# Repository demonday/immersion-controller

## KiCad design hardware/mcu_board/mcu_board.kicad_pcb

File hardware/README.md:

"Smart" Immersion Controller

See https://www.notion.so/niallgormley/Smart-Domestic-Immersion-Heater-Controller-AquaHeatIQ-cdcf95fe5f9b4179aaec39e1e94fd0bb

# Notes

## 11/11/2023 - Initial Prototype Iteration

### Results from assembly and first tests.

- Incorrect Footprint for choke (L2)
- 3.3v Power has some high freq (~20kHz) noise, and some voltage drop when relays activated.
- Relay configuration. Insufficient capacity (10A, needs ~13A) on relay NC config that I used to ensure only one relay activates at any one time.
- I wired all the temp sensors onto one jack, this kinda worked okay, and am getting temp readings, but getting "Sensor CRC errors" so its missing readings intermittently

### Ideas for v2 prototype iteration

- Change layout to match back mount for existing Horstmann mounting box. Remove earth terminal and align wiring. ✔️
- Redesign relay control circuit so that control circuit ensures that only is activated rather than relay wiring. ✔️
- Move indicator LEDs to MCU board. ✔️
- Add some capacitors/inductors to reduce PSU noise and voltage drop upon relay activation. ✔️
- Add support for a SCT-013-000 Current Sensor to measure power.
- Fix third-party KiCad libraries in projects/git. ✔️
- Find a better way of connecting the temp sensors? ✔️

## 05/12/2023 - v2 Iteration Observations

### Ideas for v3 prototype iteration

- Move LED connector to power board (left), and move the connector to the MCU board to the.
- Change the connectors so they are PH type
- Check does the rotary encoder switch need to be on a pull up rather than a pull down.
- Move position of temp sensor plug. Sticking out the bottom is probably better/safer.
- Change the pins used for the as they overlap with the onboard RGB of the v1 dev board (https://docs.espressif.com/projects/esp-idf/en/latest/esp32s3/hw-reference/esp32s3/user-guide-devkitc-1-v1.0.html)
- Move the RTC module position as it wont fit.

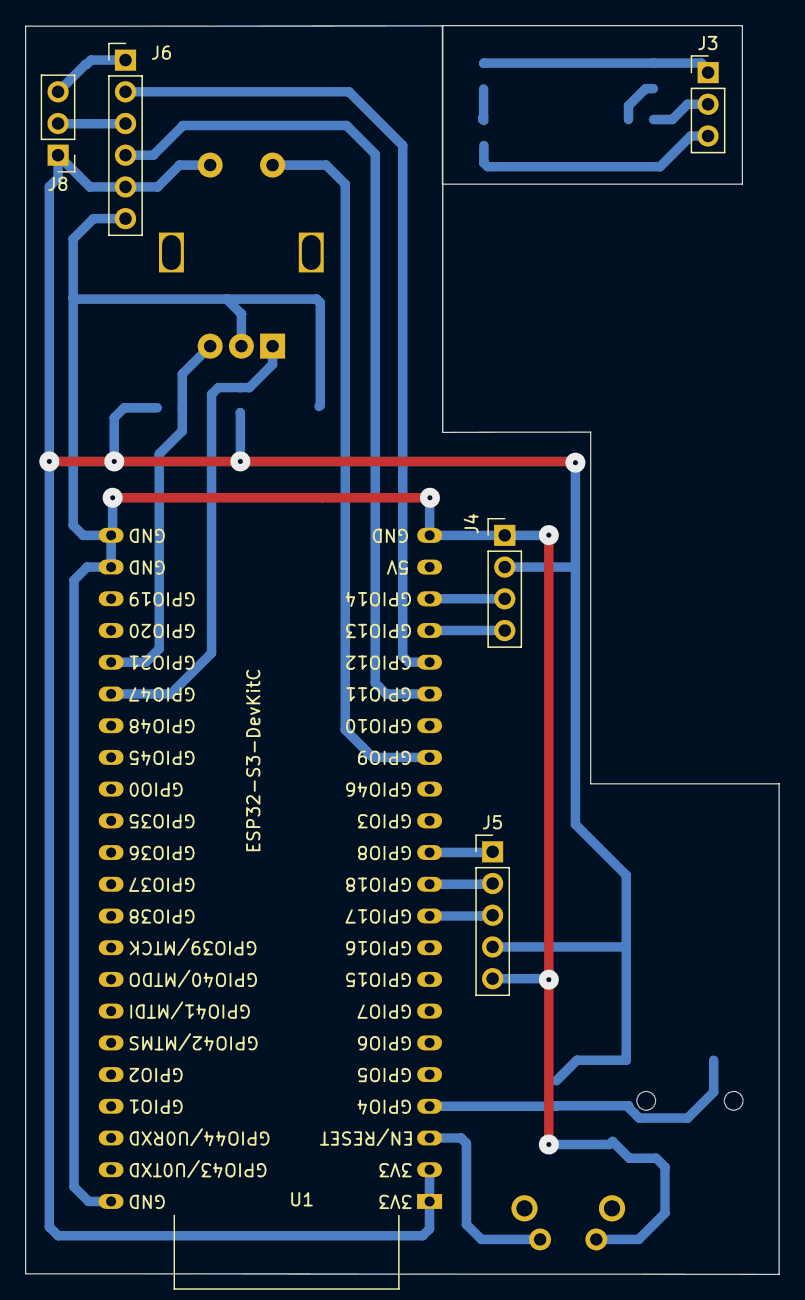
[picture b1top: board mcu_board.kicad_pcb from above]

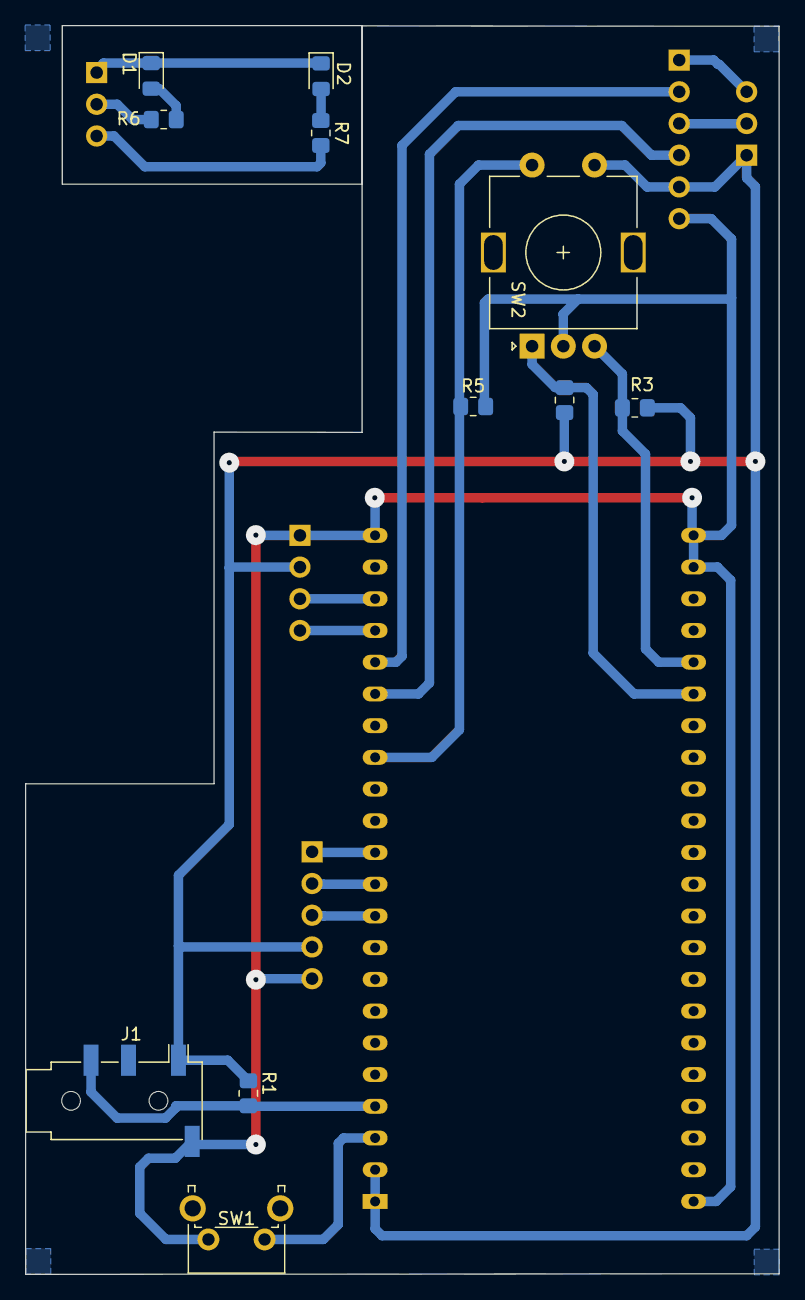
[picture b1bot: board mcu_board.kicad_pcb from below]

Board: 2 copper layers, 60.3 x 100.0 mm, 17 parts (11 on the bottom side), 21 nets.

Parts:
D1: LED_BT; D_0805_2012Metric_Pad1.15x1.40mm_HandSolder
D2: LED_OP; D_0805_2012Metric_Pad1.15x1.40mm_HandSolder
J1: TEMP; Jack_3.5mm_PJ320D_Horizontal
J3: LEDS_IN; PinHeader_1x03_P2.54mm_Vertical
J4: DISPLAY; PinHeader_1x04_P2.54mm_Vertical
J5: RTC; PinHeader_1x05_P2.54mm_Vertical
J6: MCU; PinHeader_1x06_P2.54mm_Vertical
J8: LEDS_OUT; PinHeader_1x03_P2.54mm_Vertical
R1: 4k7; R_0805_2012Metric_Pad1.20x1.40mm_HandSolder
R2, R3, R5: 10K; R_0805_2012Metric_Pad1.20x1.40mm_HandSolder
R6, R7: 330R; R_0805_2012Metric_Pad1.20x1.40mm_HandSolder
SW1: RESET; SW_Tactile_SPST_Angled_PTS645Vx39-2LFS
SW2: RotaryEncoder_Switch; RotaryEncoder_Alps_EC11E-Switch_Vertical_H20mm
U1: ESP32-S3-DevKitC

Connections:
+3.3V: J1.T, J4.2, J5.4, J6.5, J8.1, R1.2, R2.1, R3.1, SW2.S1, U1.1 (3V3), U1.2 (3V3)
DISPLAY_SCL: J4.3, U1.20 (GPIO14/ADC2_CH3)
DISPLAY_SDA: J4.4, U1.19 (GPIO13/ADC2_CH2)
GND: J1.S, J4.1, J5.5, J6.6, R5.2, SW1.2 (B), SW2.C, U1.22 (GND), U1.23 (GND), U1.24 (GND), U1.44 (GND)
LED_BOOST: J6.3, J8.2
LED_OFFPEAK: J6.1, J8.3
unnamed: D1.2 (A), R6.1
unnamed: D1.1 (K), D2.1 (K), J3.1
unnamed: D2.2 (A), R7.1
unnamed: J3.2, R6.2
unnamed: J3.3, R7.2
RELAY_BOOST: J6.4, U1.17 (GPIO11/ADC2_CH0)
RELAY_OFFPEAK: J6.2, U1.18 (GPIO12/ADC2_CH1)
RESET: SW1.1 (A), U1.3 (CHIP_PU)
ROT_CLK: R2.2, SW2.A, U1.28 (GPIO47)
ROT_DT: R3.2, SW2.B, U1.27 (GPIO21)
ROT_SW: R5.1, SW2.S2, U1.15 (GPIO9/ADC1_CH8)
RTC_SCK: J5.2, U1.11 (GPIO18/ADC2_CH7)
RTC_SDA: J5.3, U1.10 (GPIO17/ADC2_CH6)
RTC_SQW: J5.1, U1.12 (GPIO8/ADC1_CH7)
WATERTEMP_DATA: J1.R2, R1.1, U1.4 (GPIO4/ADC1_CH3)

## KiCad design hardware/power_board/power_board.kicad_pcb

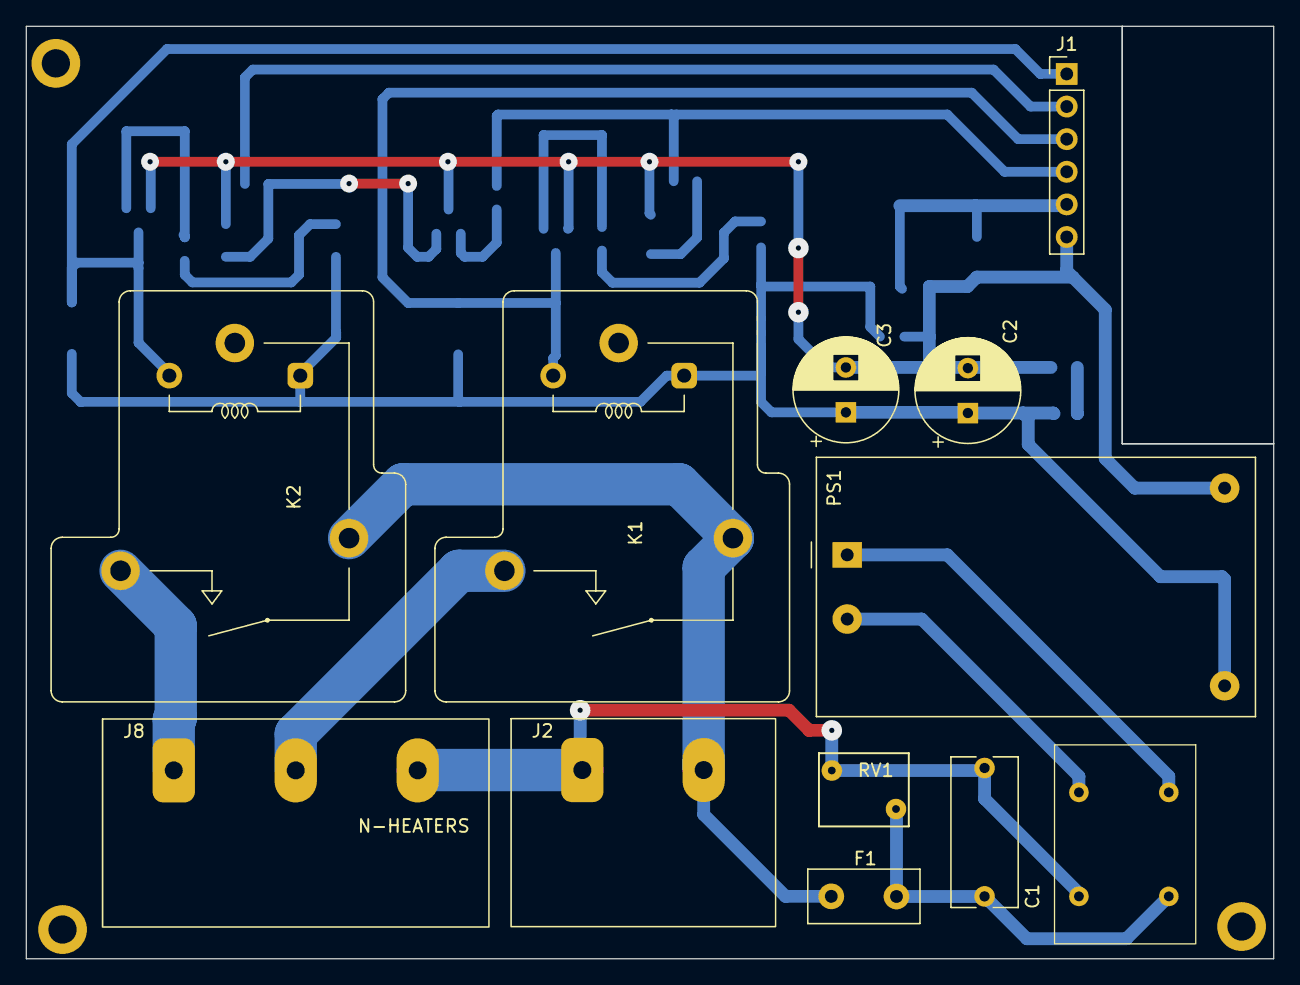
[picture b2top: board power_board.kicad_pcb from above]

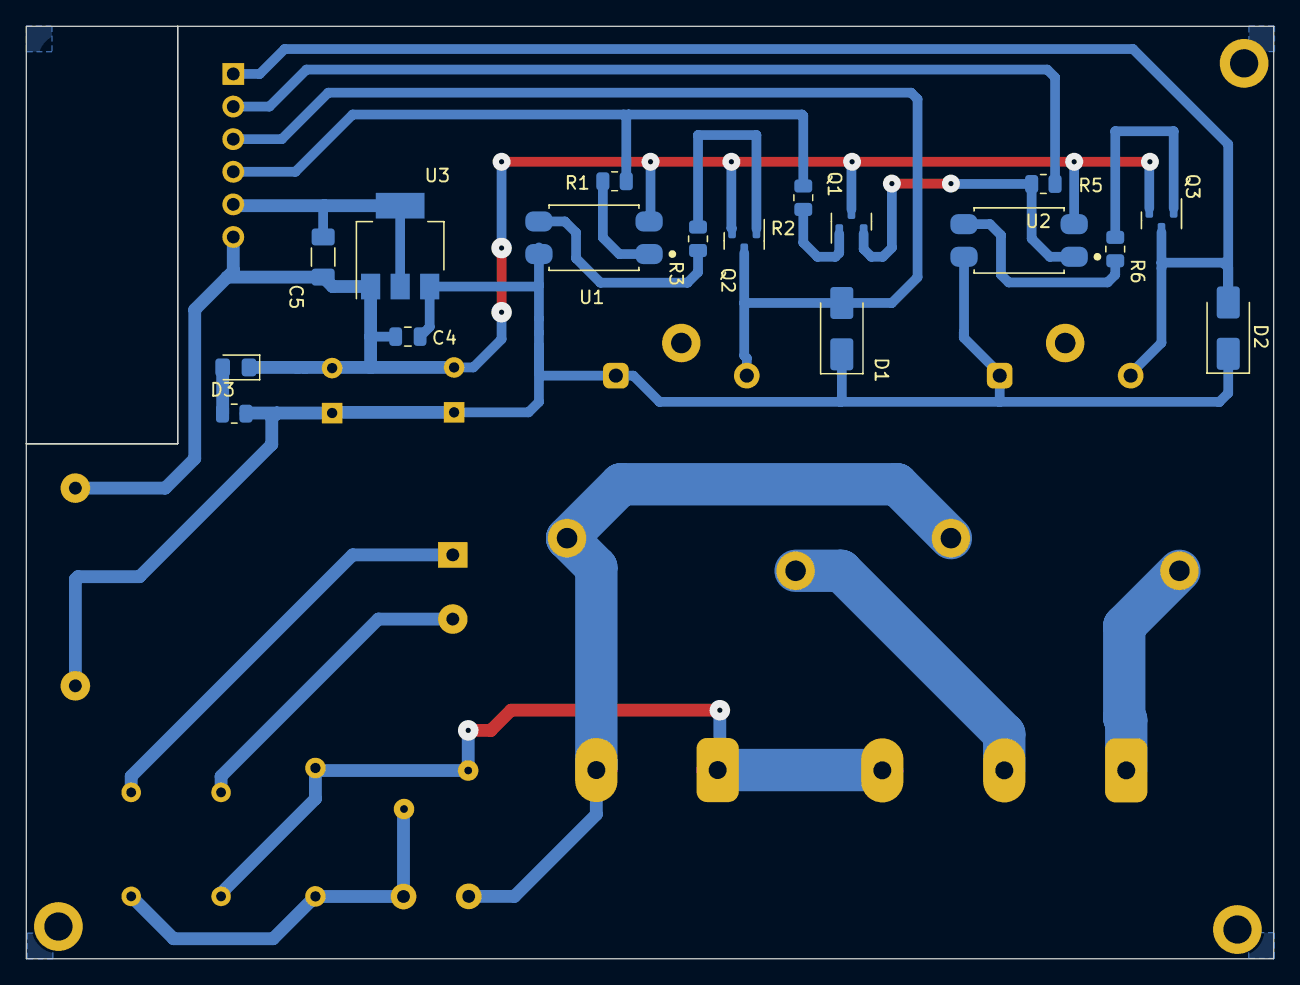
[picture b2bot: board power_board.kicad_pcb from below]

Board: 2 copper layers, 97.2 x 72.6 mm, 29 parts (17 on the bottom side), 22 nets.

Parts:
C1: 0.1uF; C_Rect_L11.5mm_W5.0mm_P10.00mm_MKT
C2: 470uF; CP_Radial_D8.0mm_P3.50mm
C3: 1uF; CP_Radial_D8.0mm_P3.50mm
C4: 10uF; C_0805_2012Metric
C5: 22uF; C_1206_3216Metric_Pad1.33x1.80mm_HandSolder
D1, D2: US1M; D_SMA
D3: LED; LED_0805_2012Metric_Pad1.15x1.40mm_HandSolder
F1: 500 mA; Fuse_Littelfuse_395Series
J1: MCU; PinHeader_1x06_P2.54mm_Vertical
J2: MAINS_IN; HB9500-9.5-2P
J8: HEATER; HB9500-9.5-3P
K1: BOOST; Relay_SPST_RAYEX-L90A
K2: OFFPEAK; Relay_SPST_RAYEX-L90A
L1: 15mH 500mA; CHOKE UU9.8
PS1: HLK-PM01; Converter_ACDC_HiLink_HLK-PMxx
Q1, Q2, Q3: MMBT3904; SOT-23
R1, R5: 470; R_0805_2012Metric
R2: 1k; R_0805_2012Metric
R3, R6: 200; R_0805_2012Metric
R8: 330; R_0805_2012Metric
RV1: 10D561; RV_Disc_D7mm_W5.7mm_P5mm
U1, U2: PC817; SOIC254P975X460-4N
U3: AMS1117-3.3; SOT-223-3_TabPin2

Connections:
+3.3V: C5.1, J1.5, U3.2 (VO)
+5V: C2.1, C3.1, C4.1, D1.1 (K), D2.1 (K), K1.A1, K2.A1, PS1.4 (+Vout), R8.1, U1.4, U2.4, U3.3 (VI)
GND: C2.2, C3.2, C4.2, C5.2, D3.1 (K), J1.6, PS1.3 (-Vout), Q1.3 (C), Q2.2 (E), Q3.2 (E), U1.2, U2.2, U3.1 (GND)
LED_BOOST: D1.2 (A), J1.3, K1.A2, Q2.3 (C)
LED_OFFPEAK: D2.2 (A), J1.1, K2.A2, Q3.3 (C)
MAINSIN_L: F1.1, J2.2, K1.13B, K2.13B
MAINSIN_N: C1.2, J2.1, J8.3, L1.2, RV1.2
unnamed: C1.1, F1.2, L1.1, RV1.1
unnamed: D3.2 (A), R8.2
unnamed: J8.1, K2.14
unnamed: J8.2, K1.14
unnamed: L1.4, PS1.1 (AC/L)
unnamed: L1.3, PS1.2 (AC/N)
unnamed: Q1.1 (B), R2.2
unnamed: Q1.2 (E), R5.1, U2.1
unnamed: Q2.1 (B), R3.2
unnamed: Q3.1 (B), R6.2
unnamed: R1.1, U1.1
unnamed: R3.1, U1.3
unnamed: R6.1, U2.3
RELAY_BOOST: J1.4, R1.2, R2.1
RELAY_OFFPEAK: J1.2, R5.2

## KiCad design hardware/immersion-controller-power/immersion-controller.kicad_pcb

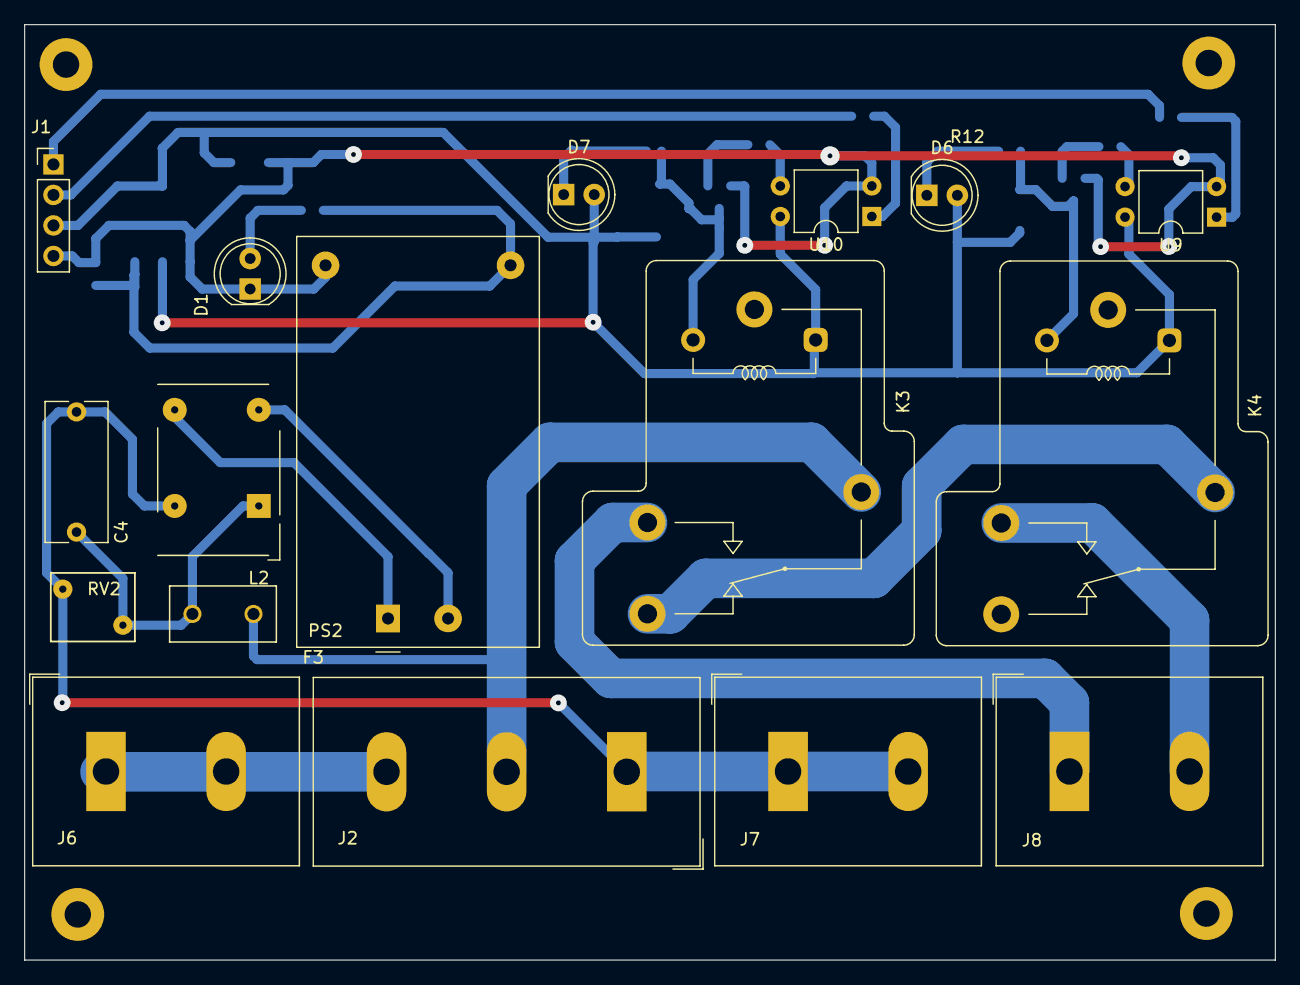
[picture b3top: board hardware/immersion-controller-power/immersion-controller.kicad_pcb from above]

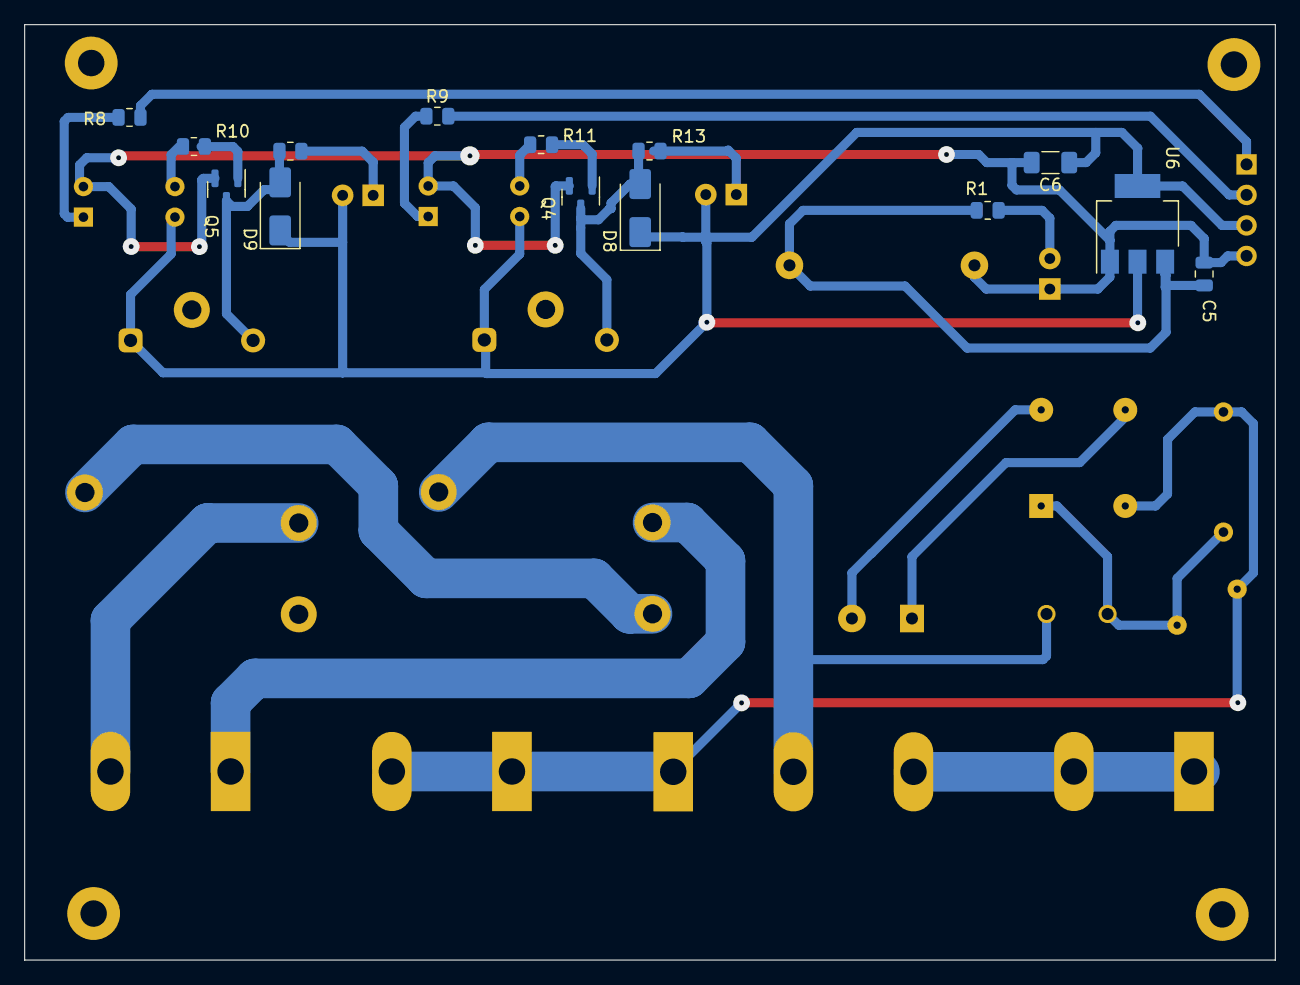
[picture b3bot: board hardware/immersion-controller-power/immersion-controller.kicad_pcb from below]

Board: 2 copper layers, 104.1 x 77.9 mm, 31 parts (14 on the bottom side), 25 nets.

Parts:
C4: 0.1uF; C_Rect_L11.5mm_W5.0mm_P10.00mm_MKT
C5: 10uF; C_0805_2012Metric
C6: 22uF; C_1206_3216Metric_Pad1.33x1.80mm_HandSolder
D1, D6, D7: LED; LED_D5.0mm_Clear
D8, D9: US1M; D_SMA
F3: 500 mA; FUSE_BK_PCE-5-R
J1: MCU; PinHeader_1x04_P2.54mm_Vertical
J2: MAINS_IN; TerminalBlock_Dinkle_DT-55-B01X-03_P10.00mm
J6: HEATER-E; TerminalBlock_Dinkle_DT-55-B01X-02_P10.00mm
J7: HEATER-N; TerminalBlock_Dinkle_DT-55-B01X-02_P10.00mm
J8: HEATER-L; TerminalBlock_Dinkle_DT-55-B01X-02_P10.00mm
K3: HEATER-BOTTOM; Relay_SPDT_RAYEX-L90
K4: HEATER-TOP; Relay_SPDT_RAYEX-L90
L2: 15mH 500mA; Choke_Schaffner_RN204-04-9.0x14.0mm
PS2: HLK-PM01; Converter_ACDC_HiLink_HLK-PMxx
Q4, Q5: MMBT3904; SOT-23
R1, R12, R13: 330; R_0805_2012Metric
R8, R9: 470; R_0805_2012Metric
R10, R11: 200; R_0805_2012Metric
RV2: 10D561; RV_Disc_D7mm_W5.7mm_P5mm
U6: AMS1117-3.3; SOT-223-3_TabPin2
U9, U10: PC817; DIP-4_W7.62mm

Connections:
+3.3V: C6.1, D6.2 (A), D7.2 (A), D8.1 (K), D9.1 (K), J1.3, K3.A1, K4.A1, U6.2 (VO), U9.4, U10.4
+5V: C5.1, PS2.4 (+Vout), R1.1, U6.3 (VI)
GND: C5.2, C6.2, D1.1 (K), J1.4, PS2.3 (-Vout), Q4.2 (E), Q5.2 (E), U6.1 (GND), U9.2, U10.2
MAINSIN_E: J2.3, J6.1, J6.2
MAINSIN_L: F3.1, J2.2, K3.11B
MAINSIN_N: C4.2, J2.1, J7.1, J7.2, L2.2, RV2.2
unnamed: C4.1, F3.2, L2.1, RV2.1
unnamed: D1.2 (A), R1.2
unnamed: D6.1 (K), R12.1
unnamed: D7.1 (K), R13.1
unnamed: D8.2 (A), K3.A2, Q4.3 (C), R13.2
unnamed: D9.2 (A), K4.A2, Q5.3 (C), R12.2
unnamed: J8.1, K3.14
unnamed: J8.2, K4.14
unnamed: K3.12, K4.11B
unnamed: L2.4, PS2.1 (AC/L)
unnamed: L2.3, PS2.2 (AC/N)
unnamed: Q4.1 (B), R11.2
unnamed: Q5.1 (B), R10.2
unnamed: R8.1, U9.1
unnamed: R9.1, U10.1
unnamed: R10.1, U9.3
unnamed: R11.1, U10.3
RELAY_BOTTOM: J1.2, R9.2
RELAY_TOP: J1.1, R8.2

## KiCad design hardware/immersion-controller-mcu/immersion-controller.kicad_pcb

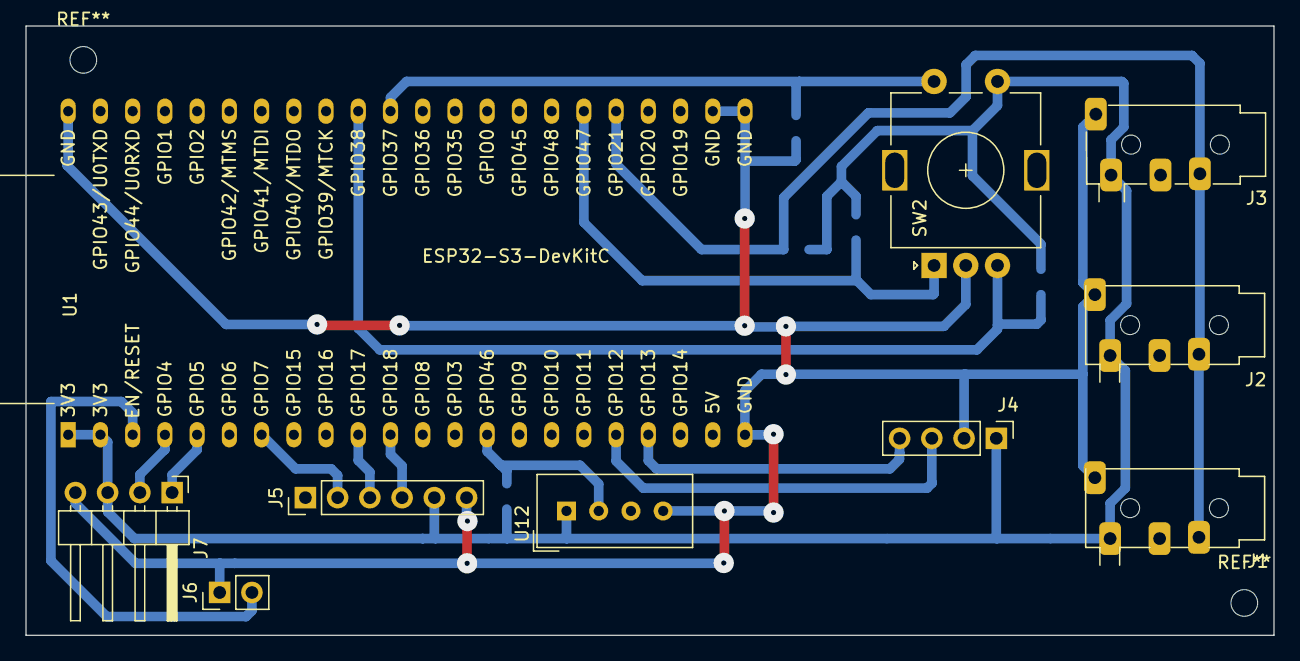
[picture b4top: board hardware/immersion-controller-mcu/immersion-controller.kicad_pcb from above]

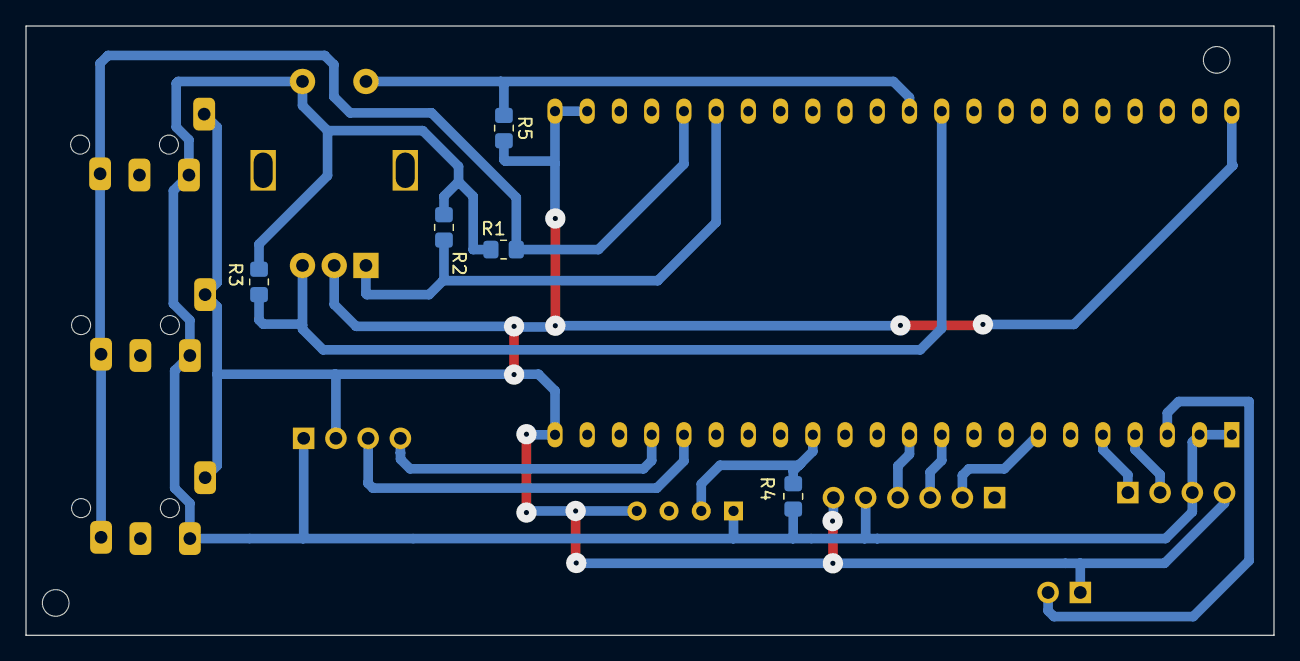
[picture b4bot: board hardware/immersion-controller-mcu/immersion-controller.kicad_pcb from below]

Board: 2 copper layers, 98.4 x 48.0 mm, 15 parts (5 on the bottom side), 15 nets.

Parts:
J1: TANK-TOP; Jack_3.5mm_PJ320D_Horizontal_NG
J2: TANK-BOTTOM; Jack_3.5mm_PJ320D_Horizontal_NG
J3: COLD; Jack_3.5mm_PJ320D_Horizontal_NG
J4: DISPLAY; PinHeader_1x04_P2.54mm_Vertical
J5: RTC; PinHeader_1x06_P2.54mm_Vertical
J6: Conn_01x02_Pin; PinHeader_1x02_P2.54mm_Vertical
J7: MCU; PinHeader_1x04_P2.54mm_Horizontal
R1, R4: 4k7; R_0805_2012Metric_Pad1.20x1.40mm_HandSolder
R2, R3, R5: 10K; R_0805_2012Metric_Pad1.20x1.40mm_HandSolder
SW2: RotaryEncoder_Switch; RotaryEncoder_Alps_EC11E-Switch_Vertical_H20mm
U1: ESP32-S3-DevKitC
U12: DHT11; Aosong_DHT11_5.5x12.0_P2.54mm

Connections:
+3.3V: J1.T, J2.T, J3.T, J4.1, J5.5, J7.3, R1.2, R2.1, R3.1, R4.2, SW2.S1, U1.1 (3V3), U1.2 (3V3), U12.1 (VCC)
DHT_DATA: R4.1, U1.14 (GPIO46), U12.2 (IO)
DISPLAY_SCL: J4.3, U1.18 (GPIO12/ADC2_CH1)
DISPLAY_SDA: J4.4, U1.19 (GPIO13/ADC2_CH2)
GND: J1.S, J2.S, J3.S, J4.2, J5.6, J6.1, J7.4, R5.2, SW2.C, U1.22 (GND), U1.23 (GND), U1.24 (GND), U1.44 (GND), U12.4 (GND)
RELAY_BOTTOM: J7.1, U1.5 (GPIO5/ADC1_CH4)
RELAY_TOP: J7.2, U1.4 (GPIO4/ADC1_CH3)
RESET: J6.2, U1.3 (CHIP_PU)
ROT_CLK: R2.2, SW2.A, U1.28 (GPIO47)
ROT_DT: R3.2, SW2.B, U1.35 (GPIO38)
ROT_SW: R5.1, SW2.S2, U1.34 (GPIO37)
RTC_SCK: J5.3, U1.10 (GPIO17/ADC2_CH6)
RTC_SDA: J5.4, U1.11 (GPIO18/ADC2_CH7)
RTC_SQW: J5.2, U1.7 (GPIO7/ADC1_CH6)
WATERTEMP_DATA: J1.R2, J2.R2, J3.R2, R1.1, U1.27 (GPIO21)

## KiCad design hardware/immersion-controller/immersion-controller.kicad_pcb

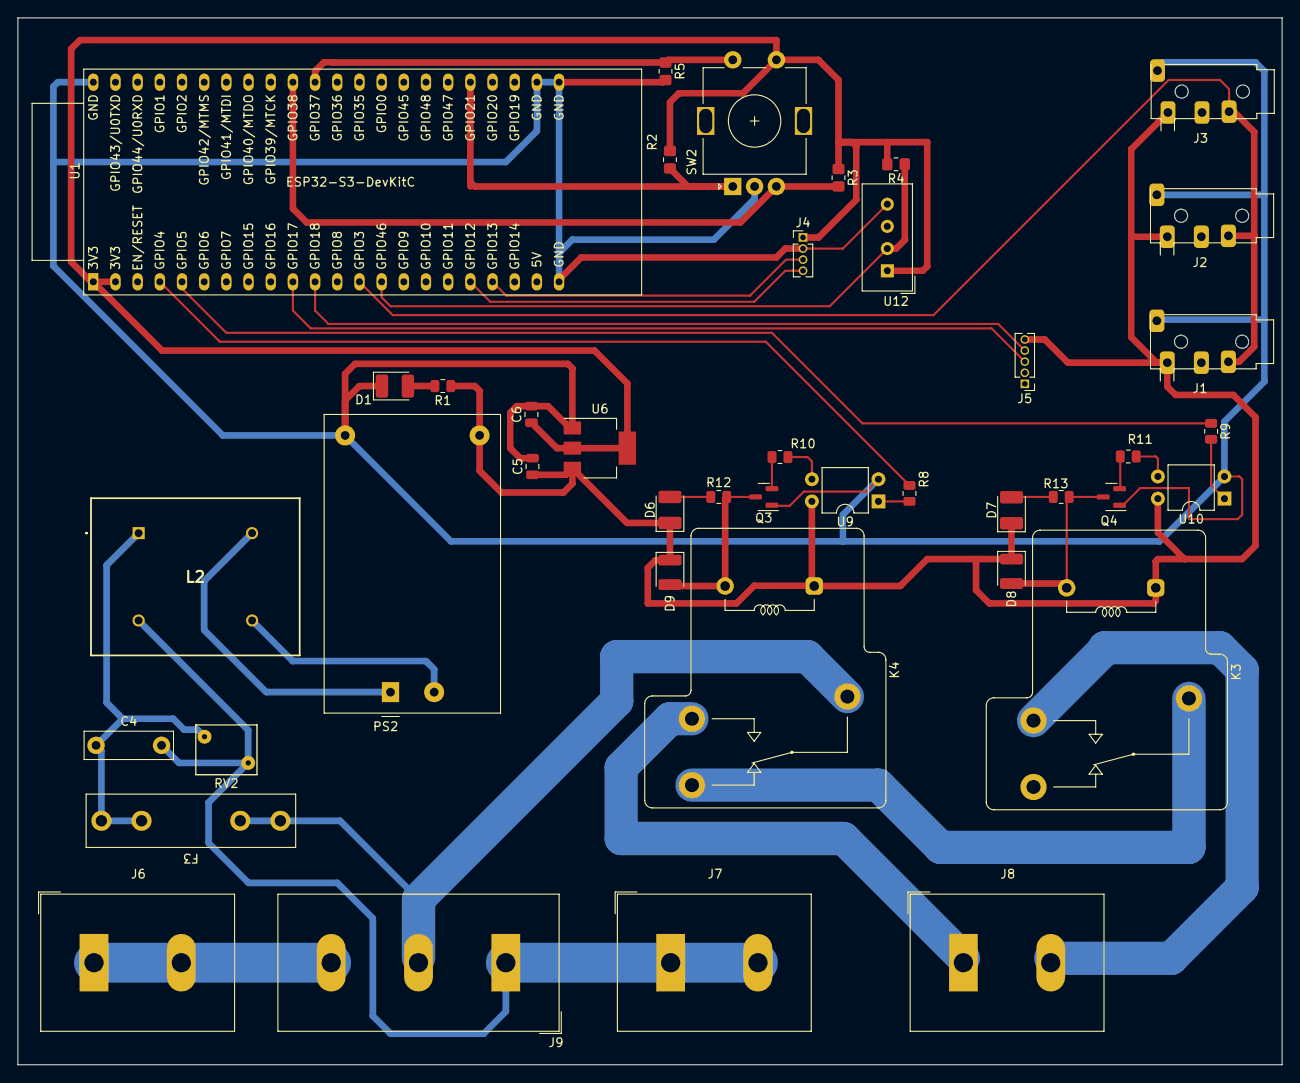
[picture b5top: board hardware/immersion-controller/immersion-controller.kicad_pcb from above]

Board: 2 copper layers, 144.8 x 119.9 mm, 42 parts (0 on the bottom side), 34 nets.

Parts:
C4: 0.1uF; C_Rect_L10.0mm_W3.0mm_P7.50mm_MKS4
C5: 10uF; C_0805_2012Metric
C6: 22uF; C_0805_2012Metric
D1, D6, D7: LED; D_1210_3225Metric_Pad1.42x2.65mm_HandSolder
D8, D9: 1N4007; D_1210_3225Metric
F3: 1A; Fuseholder_Littelfuse_100_series_5x20mm
J1: TANK-TOP; Jack_3.5mm_PJ320D_Horizontal_NG
J2: TANK-BOTTOM; Jack_3.5mm_PJ320D_Horizontal_NG
J3: COLD; Jack_3.5mm_PJ320D_Horizontal_NG
J4: DISPLAY; PinHeader_1x04_P1.27mm_Vertical
J5: RTC; PinHeader_1x05_P1.27mm_Vertical
J6: HEATER-E; TerminalBlock_Dinkle_DT-55-B01X-02_P10.00mm
J7: HEATER-N; TerminalBlock_Dinkle_DT-55-B01X-02_P10.00mm
J8: HEATER-L; TerminalBlock_Dinkle_DT-55-B01X-02_P10.00mm
J9: MAINS_IN; TerminalBlock_Dinkle_DT-55-B01X-03_P10.00mm
K3: HEATER-BOTTOM; Relay_SPDT_RAYEX-L90S
K4: HEATER-TOP; Relay_SPDT_RAYEX-L90S
L2: 15mH 500mA; ALFT03A11
PS2: HLK-PM01; Converter_ACDC_HiLink_HLK-PMxx
Q3, Q4: 2N3904; SOT-23
R1, R12, R13: 330; R_0805_2012Metric
R2, R3, R5: 10K; R_0805_2012Metric_Pad1.20x1.40mm_HandSolder
R4: 4k7; R_0805_2012Metric_Pad1.20x1.40mm_HandSolder
R8, R9: 470; R_0805_2012Metric
R10, R11: 200; R_0805_2012Metric
RV2: 10D561; RV_Disc_D7mm_W5.7mm_P5mm
SW2: RotaryEncoder_Switch; RotaryEncoder_Alps_EC11E-Switch_Vertical_H20mm
U1: ESP32-S3-DevKitC
U6: AMS1117-3.3; SOT-223-3_TabPin2
U9, U10: PC817; DIP-4_W7.62mm
U12: DHT11; Aosong_DHT11_5.5x12.0_P2.54mm

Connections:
+3.3V: C6.1, J4.1, R2.1, R3.1, R4.2, SW2.S1, U1.1 (3V3), U1.2 (3V3), U6.2 (VO), U12.1 (VCC)
+5V: C5.1, D6.1 (K), D7.1 (K), D8.1 (K), D9.1 (K), J1.T, J2.T, J3.T, J5.5, K3.A1, K4.A1, PS2.4 (+Vout), R1.1, U6.3 (VI), U9.4, U10.4
DHT_DATA: R4.1, U1.14 (GPIO46), U12.2 (IO)
DISPLAY_SCK: J4.3, U1.19 (GPIO13/ADC2_CH2)
DISPLAY_SDA: J4.4, U1.18 (GPIO12/ADC2_CH1)
GND: C5.2, C6.2, D1.1 (K), J1.S, J2.S, J3.S, J4.2, PS2.3 (-Vout), Q3.1 (E), Q4.1 (E), R5.2, SW2.C, U1.22 (GND), U1.23 (GND), U1.24 (GND), U1.44 (GND), U6.1 (GND), U9.2, U10.2, U12.4 (GND)
MAINSIN_E: J6.1, J6.2, J9.3
MAINSIN_L: F3.1, J9.2, K4.11
MAINSIN_N: C4.2, J7.1, J7.2, J9.1, L2.2, RV2.2
unnamed: C4.1, F3.2, L2.1, RV2.1
unnamed: D1.2 (A), R1.2
unnamed: D6.2 (A), R12.1
unnamed: D7.2 (A), R13.1
unnamed: D8.2 (A), K3.A2, Q4.3 (C), R13.2
unnamed: D9.2 (A), K4.A2, Q3.3 (C), R12.2
unnamed: J8.1, K4.14
unnamed: J8.2, K3.14
unnamed: K3.11, K4.12
unnamed: L2.4, PS2.1 (AC/L)
unnamed: L2.3, PS2.2 (AC/N)
unnamed: Q3.2 (B), R10.2
unnamed: Q4.2 (B), R11.2
unnamed: R8.2, U9.1
unnamed: R9.2, U10.1
unnamed: R10.1, U9.3
unnamed: R11.1, U10.3
RELAY_BOTTOM: R9.1, U1.5 (GPIO5/ADC1_CH4)
RELAY_TOP: R8.1, U1.4 (GPIO4/ADC1_CH3)
ROT_CLK: R2.2, SW2.A, U1.27 (GPIO21)
ROT_DT: R3.2, SW2.B, U1.35 (GPIO38)
ROT_SW: R5.1, SW2.S2, U1.34 (GPIO37)
RTC_SCK: J5.3, U1.10 (GPIO17/ADC2_CH6)
RTC_SDA: J5.4, U1.11 (GPIO18/ADC2_CH7)
WATERTEMP_DATA: J1.R2, J2.R2, J3.R2, U1.13 (GPIO3/ADC1_CH2)

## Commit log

2023-07-31 First Iteration
2023-07-31 Fix .gitignore to ignore kicad backups
2023-08-11 Validated prototype
2023-08-23 Added missing pullup resistor and reset pin
2023-08-23 SPST Relay
2023-10-19 debugged prototype
2023-11-11 Initial Prototype results
2023-11-11 remove library folders, before restructing them
2023-11-11 rename kicad projects
2023-11-12 v2 Power/Relay PCB
2023-11-12 Fixing Modules
2023-11-12 Fix module paths
2023-11-13 Refactored PCBs for v2. See README
2023-11-15 v2 layout changes to fit in bax
2023-11-16 Laypout tweaks to fit case
2023-11-17 v2 Boards for fabrication
2023-11-22 Add missing holes and fabrication marks
2023-11-24 minor layout tweaks
2023-11-25 fix boards so they components are on the correct side lol
2023-11-27 move screw position
2023-12-01 minor tweaks
2023-12-05 v3 first draft
2023-12-05 Update README.md to reflect improvements needed in v3 rev
